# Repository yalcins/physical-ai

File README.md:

# Physical AI – 11/12. Sınıf Robotik Projesi

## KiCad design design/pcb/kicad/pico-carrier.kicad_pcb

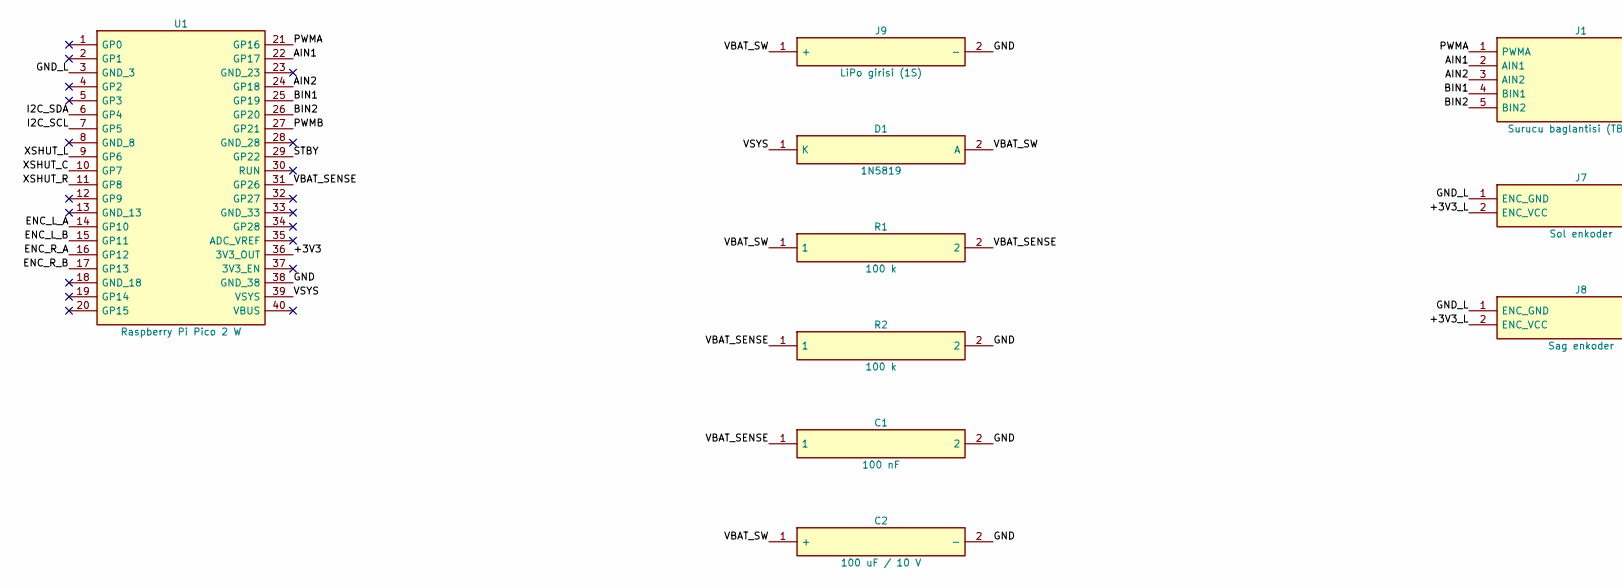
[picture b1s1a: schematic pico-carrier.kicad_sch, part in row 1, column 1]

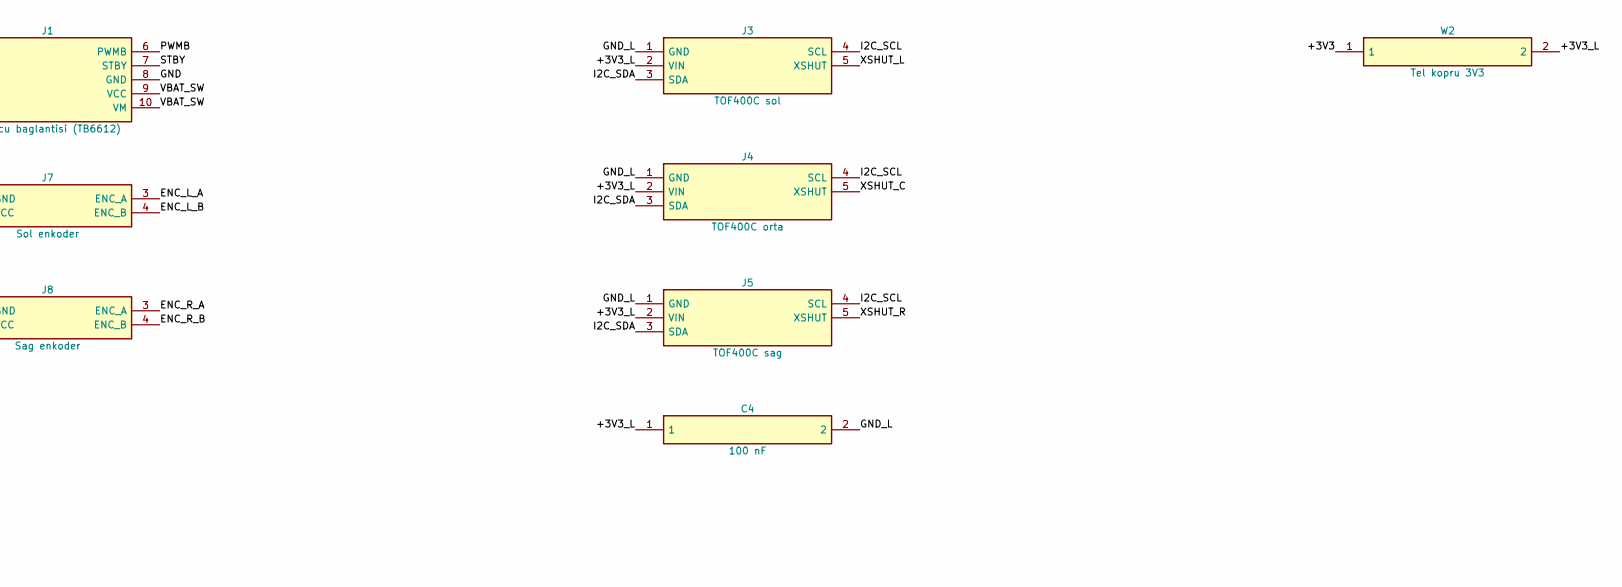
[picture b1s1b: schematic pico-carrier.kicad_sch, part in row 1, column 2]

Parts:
C1, C4: 100 nF; C_Disc_D5.0mm_W2.5mm_P5.00mm
C2: 100 uF / 10 V; CP_Radial_D6.3mm_P2.50mm
D1: 1N5819; D_DO-41_SOD81_P2.54mm_Vertical_KathodeUp
J1: Surucu baglantisi (TB6612); PinHeader_1x10_P2.54mm_Vertical
J3: TOF400C sol; PinSocket_1x05_P2.54mm_Vertical
J4: TOF400C orta; PinSocket_1x05_P2.54mm_Vertical
J5: TOF400C sag; PinSocket_1x05_P2.54mm_Vertical
J7: Sol enkoder; PinHeader_1x04_P2.54mm_Vertical
J8: Sag enkoder; PinHeader_1x04_P2.54mm_Vertical
J9: LiPo girisi (1S); JST_PH_B2B-PH-K_1x02_P2.00mm_Vertical
R1, R2: 100 k; R_Axial_DIN0207_L6.3mm_D2.5mm_P2.54mm_Vertical
U1: Raspberry Pi Pico 2 W; RaspberryPi_Pico_THT
W2: Tel kopru 3V3; WireLink_P30.48mm

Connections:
+3V3: U1.36 (3V3_OUT), W2.1
+3V3_L: C4.1, J3.2 (VIN), J4.2 (VIN), J5.2 (VIN), J7.2 (ENC_VCC), J8.2 (ENC_VCC), W2.2
AIN1: J1.2 (AIN1), U1.22 (GP17)
AIN2: J1.3 (AIN2), U1.24 (GP18)
BIN1: J1.4 (BIN1), U1.25 (GP19)
BIN2: J1.5 (BIN2), U1.26 (GP20)
ENC_L_A: J7.3 (ENC_A), U1.14 (GP10)
ENC_L_B: J7.4 (ENC_B), U1.15 (GP11)
ENC_R_A: J8.3 (ENC_A), U1.16 (GP12)
ENC_R_B: J8.4 (ENC_B), U1.17 (GP13)
GND: C1.2, C2.2 (-), J1.8 (GND), J9.2 (-), R2.2, U1.38 (GND_38)
GND_L: C4.2, J3.1 (GND), J4.1 (GND), J5.1 (GND), J7.1 (ENC_GND), J8.1 (ENC_GND), U1.3 (GND_3)
I2C_SCL: J3.4 (SCL), J4.4 (SCL), J5.4 (SCL), U1.7 (GP5)
I2C_SDA: J3.3 (SDA), J4.3 (SDA), J5.3 (SDA), U1.6 (GP4)
PWMA: J1.1 (PWMA), U1.21 (GP16)
PWMB: J1.6 (PWMB), U1.27 (GP21)
STBY: J1.7 (STBY), U1.29 (GP22)
VBAT_SENSE: C1.1, R1.2, R2.1, U1.31 (GP26)
VBAT_SW: C2.1 (+), D1.2 (A), J1.9 (VCC), J1.10 (VM), J9.1 (+), R1.1
VSYS: D1.1 (K), U1.39 (VSYS)
XSHUT_C: J4.5 (XSHUT), U1.10 (GP7)
XSHUT_L: J3.5 (XSHUT), U1.9 (GP6)
XSHUT_R: J5.5 (XSHUT), U1.11 (GP8)

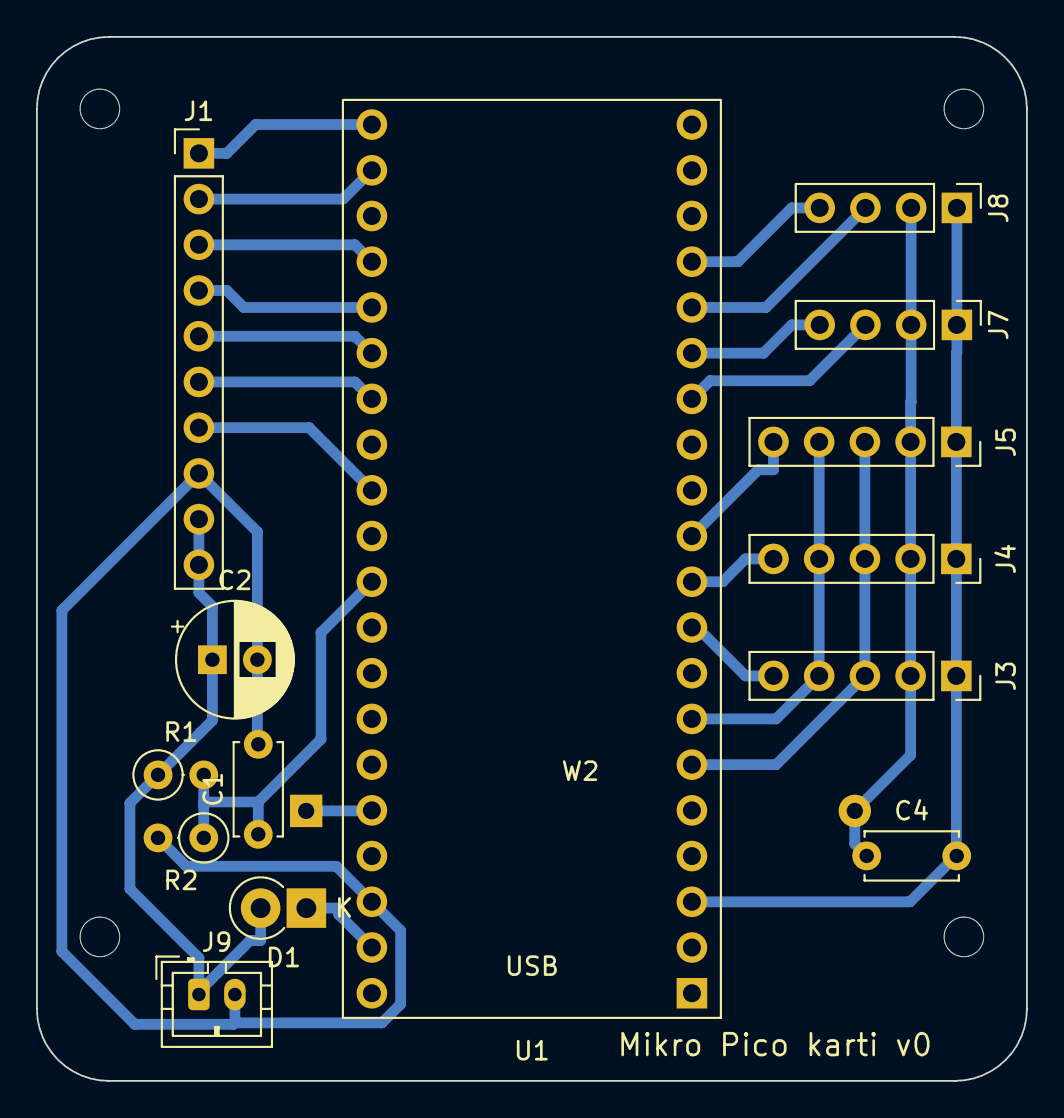
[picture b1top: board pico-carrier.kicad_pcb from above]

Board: 2 copper layers, 55.0 x 58.0 mm, 19 parts (0 on the bottom side), 23 nets.

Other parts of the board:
H1, H2, H3, H4: MountingHole_2.2mm_M2

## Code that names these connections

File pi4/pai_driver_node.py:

"""Pi 4 robot surucusu (TASLAK): /cmd_vel -> motorlar, ToF -> /tof_*/range.

Gazebo ikiziyle ayni konulari yayinlar; boylece pai_robot.RosRobot ikisinde de calisir.
DURUM: Pi 4 uzerinde henuz denenmedi. Pin numaralari ONERIDIR (sanal tasarim, docs/data/wiring.json);
farkli kablolanirsa PINS sozlugunu gercege gore degistir.
ToF okuma ve adres atama tof.py icinde (sahte sensorlerle test edildi, gercek sensorle degil).
"""
import math
import signal

import rclpy
from geometry_msgs.msg import Twist
from rclpy.executors import ExternalShutdownException
from rclpy.node import Node
from rclpy.qos import qos_profile_sensor_data
from sensor_msgs.msg import Range

from tof import ToFArray

WHEEL_RADIUS = 0.0215
WHEEL_SEPARATION = 0.115
MAX_WHEEL_RAD_S = 31.0
CMD_TIMEOUT = 0.5                    # sn: komut kesilirse dur

# TB6612FNG BCM pinleri. ONERI (sanal tasarim, docs/data/wiring.json): kablolamadan once dogrula, degisirse
# hem burayi hem wiring tablosunu (tools/design/build_all.py) guncelle. None = atanmadi (surucu baslamaz).
PINS = {'pwma': 12, 'ain1': 23, 'ain2': 24,
        'pwmb': 13, 'bin1': 25, 'bin2': 16, 'stby': 20}
# Her ToF'un XSHUT pini (I2C adres atamasi icin), sira: sol, orta, sag. ONERI.
XSHUT_PINS = (5, 6, 26)
# Enkoder pinleri (sol A,B / sag A,B) = (17, 27) / (22, 4): surucu henuz okumuyor, yalnizca kablolama icin.
TOF_NAMES = ('left', 'center', 'right')
TOF_FOV = math.radians(27)
TOF_MIN, TOF_MAX = 0.04, 4.0


class PaiDriver(Node):
    def __init__(self):
        super().__init__('pai_driver')
        if any(v is None for v in PINS.values()) or None in XSHUT_PINS:
            raise RuntimeError('PINS / XSHUT_PINS doldurulmadi: pi4/pai_driver_node.py icinde pinleri yaz.')
        from gpiozero import DigitalOutputDevice, PWMOutputDevice
        self.stby = DigitalOutputDevice(PINS['stby'], initial_value=True)
        self.left = (PWMOutputDevice(PINS['pwma']), DigitalOutputDevice(PINS['ain1']), DigitalOutputDevice(PINS['ain2']))
        self.right = (PWMOutputDevice(PINS['pwmb']), DigitalOutputDevice(PINS['bin1']), DigitalOutputDevice(PINS['bin2']))
        self.create_subscription(Twist, '/cmd_vel', self.on_cmd, 10)
        self.pubs = [self.create_publisher(Range, f'/tof_{n}/range', qos_profile_sensor_data) for n in TOF_NAMES]
        self.last_cmd = self.get_clock().now()
        self.create_timer(0.05, self.tick)      # 20 Hz: ToF oku + watchdog
        self.tof = ToFArray(XSHUT_PINS)       # adresleri atar (tof.py)

    def on_cmd(self, msg):
        self.last_cmd = self.get_clock().now()
        v, w = msg.linear.x, msg.angular.z
        self.set_motor(self.left, (v - w * WHEEL_SEPARATION / 2) / WHEEL_RADIUS)
        self.set_motor(self.right, (v + w * WHEEL_SEPARATION / 2) / WHEEL_RADIUS)

    @staticmethod
    def set_motor(motor, rad_s):
        pwm, in1, in2 = motor
        in1.value, in2.value = int(rad_s > 0), int(rad_s < 0)
        pwm.value = min(abs(rad_s) / MAX_WHEEL_RAD_S, 1.0)

    def publish_tof(self):
        """Sensor_msgs/Range, REP 117: menzil disi +inf, min'den yakin -inf (Gazebo ikiziyle ayni)."""
        now = self.get_clock().now().to_msg()
        for name, pub, r in zip(TOF_NAMES, self.pubs, self.tof.read()):
            msg = Range()
            msg.header.stamp = now
            msg.header.frame_id = f'tof_{name}'
            msg.radiation_type = Range.INFRARED
            msg.field_of_view = TOF_FOV
            msg.min_range, msg.max_range = TOF_MIN, TOF_MAX
            if r is None or r > TOF_MAX:
                msg.range = math.inf
            elif r < TOF_MIN:
                msg.range = -math.inf
            else:
                msg.range = r
            pub.publish(msg)

    def stop_motors(self):
        self.set_motor(self.left, 0.0)
        self.set_motor(self.right, 0.0)

    def tick(self):
        self.publish_tof()
        if (self.get_clock().now() - self.last_cmd).nanoseconds > CMD_TIMEOUT * 1e9:
            self.stop_motors()


def main():
    rclpy.init()
    signal.signal(signal.SIGTERM, signal.default_int_handler)   # run.sh stop: SIGTERM -> temiz cikis
    node = PaiDriver()
    try:
        rclpy.spin(node)
    except (KeyboardInterrupt, ExternalShutdownException):
        pass
    finally:
        node.stop_motors()                 # her cikista motorlar kapansin (run.sh stop SIGTERM yollar)
        node.tof.close()
        node.destroy_node()
        rclpy.try_shutdown()


if __name__ == '__main__':
    main()
